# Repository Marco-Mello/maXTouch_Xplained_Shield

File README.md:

# maxTouch-EXT-V1

Shield para liberar o EXT1 e utilizar o maXTouch XPlained

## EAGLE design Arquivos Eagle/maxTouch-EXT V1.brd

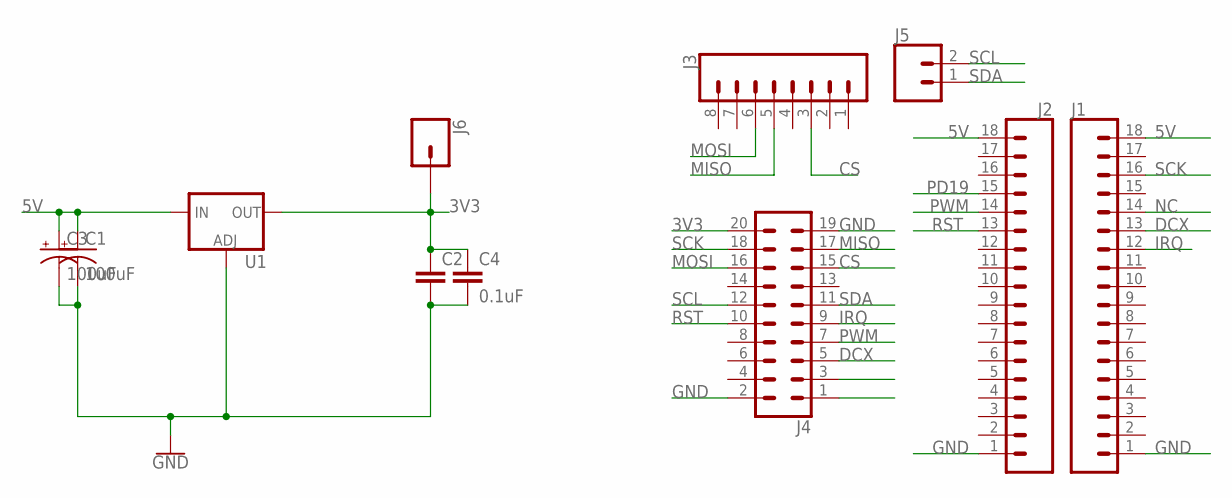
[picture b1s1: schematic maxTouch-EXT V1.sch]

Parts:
C1: 100uF; NIC_10X10.5_CAP
C2: 10uF; 0805
C3: 100uF; CPOL-RADIAL-2.5MM-6.5MM
C4: 0.1uF; CAP-PTH-SMALL-KIT
J1, J2: CONN_18SILK; 1X18
J3: CONN_08"; 1X08
J4: CONN_10X2; 2X10
J5: CONN_02; 1X02
J6: CONN_01; 1X01
U1: V_REG_LM1117SOT223; SOT223

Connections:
3V3: C2.1, C4.1, J4.20, J6.1, U1.2 (OUT), U1.4 (OUT)
5V: C1.+, C3.1 (+), J1.18, J2.18, U1.3 (IN)
CS: J3.3, J4.15
DCX: J1.13, J4.5
GND: C1.-, C2.2, C3.2 (-), C4.2, J1.1, J2.1, J4.2, J4.19, U1.1 (ADJ)
IRQ: J1.12, J4.9
MISO: J3.5, J4.17
MOSI: J3.6, J4.16
NC: J1.14
PD19: J2.15
PWM: J2.14, J4.7
RST: J2.13, J4.10
SCK: J1.16, J4.18
SCL: J4.12, J5.2
SDA: J4.11, J5.1

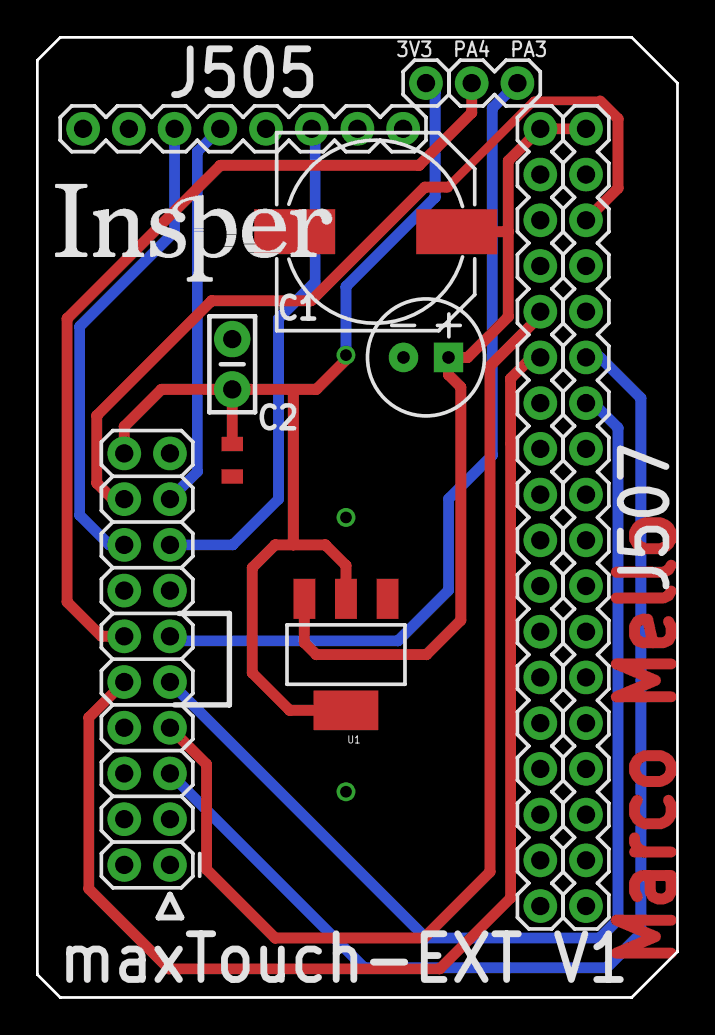
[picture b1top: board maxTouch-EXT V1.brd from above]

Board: 2 copper layers, 35.6 x 53.3 mm, 11 parts (0 on the bottom side), 13 nets.

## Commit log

2019-11-26 Upload .brd e .sch
2019-11-27 THandSMD
2019-12-09 maxTouch-EXT V1
2019-12-10 maxTouch-EXT-V1
2019-12-10 Removidos Arquivos .brd e .sch Antigos
2019-12-16 Alterado o regulador para obter todos os componentes no Brasil
2020-02-21 Pequenas Alterações no .brd
2020-02-27 Pequenas alteracoes no Layout

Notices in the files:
parts and their libraries:
SparkFun-Connectors: Licensing: Creative Commons ShareAlike 4.0 International - https://creativecommons.org/licenses/by-sa/4.0
